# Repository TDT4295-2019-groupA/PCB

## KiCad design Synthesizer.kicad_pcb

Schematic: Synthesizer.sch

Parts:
C1: 150u; C_1206_3216Metric_Pad1.42x1.75mm_HandSolder
C2: 100n; C_0805_2012Metric_Pad1.15x1.40mm_HandSolder
D1, D2, D3, D4: LED; LED_D3.0mm
FB1, FB3, FB4: Ferrite_Bead; FerriteBead_74279215
J1: USB_A; TE_1932638-3
J2: AudioJack3; Jack_3.5mm_CUI_SJ-3524-SMT_Horizontal
J3: USB_B_Micro; USB_Micro-B_GCT_USB3076-30-A
R33, R34: 33; R_1206_3216Metric_Pad1.42x1.75mm_HandSolder
R38: 100; R_1206_3216Metric_Pad1.42x1.75mm_HandSolder
R39: 160; R_1206_3216Metric_Pad1.42x1.75mm_HandSolder
R40: 250; R_1206_3216Metric_Pad1.42x1.75mm_HandSolder
R41: 400; R_1206_3216Metric_Pad1.42x1.75mm_HandSolder
SW1, SW2, SW3, SW4, SW5, SW6, SW7, SW8, SW9, SW10, SW11, SW12, SW13, SW14, SW15, SW16: SW_Push; SW_Push_1P1T_NO_6x6mm_H9.5mm
U1: TPD3S014; SOT-23-6

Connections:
+3V3: SW1.1, SW2.1, SW3.1, SW4.1, SW5.1, SW6.1, SW7.1, SW8.1, SW9.1, SW10.1, SW11.1, SW12.1, SW13.1, SW14.1, SW15.1, SW16.1; also elsewhere on the board
+5V: C2.2, J3.1, U1.3; also elsewhere on the board
/Artix7/GREEN_LED: D4.2; also elsewhere on the board
/Artix7/RED_LED: D3.2; also elsewhere on the board
/Audio DAC/OUTL: J2.R; also elsewhere on the board
/Audio DAC/OUTR: J2.T; also elsewhere on the board
/Button0: SW13.2; also elsewhere on the board
/Button1: SW1.2; also elsewhere on the board
/Button2: SW2.2; also elsewhere on the board
/Button3: SW3.2; also elsewhere on the board
/Button4: SW4.2; also elsewhere on the board
/Button5: SW5.2; also elsewhere on the board
/Button6: SW6.2; also elsewhere on the board
/Button7: SW7.2; also elsewhere on the board
/Button8: SW8.2; also elsewhere on the board
/Button9: SW9.2; also elsewhere on the board
/Button10: SW10.2; also elsewhere on the board
/Button11: SW11.2; also elsewhere on the board
/Button12: SW12.2; also elsewhere on the board
/Button13: SW15.2; also elsewhere on the board
/Button14: SW14.2; also elsewhere on the board
/Button15: SW16.2; also elsewhere on the board
/EFM32/GREEN_LED: D2.2; also elsewhere on the board
/EFM32/RED_LED: D1.2; also elsewhere on the board
/EFM32/USB_D+: R33.1; also elsewhere on the board
/EFM32/USB_D-: R34.1; also elsewhere on the board
/EFM32/USB_VBUSEN: U1.1; also elsewhere on the board
GND: C1.1, C2.1, FB1.2, FB4.2, J2.S, J3.5, J3.6, R38.1, R39.1, R40.1, R41.1, U1.2; also elsewhere on the board
unnamed: C1.2, FB3.2, J1.1
unnamed: D1.1, R38.2
unnamed: D2.1, R39.2
unnamed: D3.1, R40.2
unnamed: D4.1, R41.2
unnamed: FB1.1, J1.4
unnamed: FB3.1, U1.4
unnamed: FB4.1, J1.5
unnamed: J1.2, R34.2, U1.5
unnamed: J1.3, R33.2, U1.6

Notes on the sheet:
PCM audio source
assuming source = 8mA
resistance assuming source = 20mA

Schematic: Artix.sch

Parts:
C3, C4: 100n; C_0805_2012Metric_Pad1.15x1.40mm_HandSolder
J4: FPGA_debug; PinHeader_2x07_P2.54mm_Vertical
J7: FPGA_GPIO; 67997-410HLF
R1: 2.4k; R_1206_3216Metric_Pad1.42x1.75mm_HandSolder
R2, R4: 10k; R_1206_3216Metric_Pad1.42x1.75mm_HandSolder
R3, R5, R6, R8: 4.7k; R_1206_3216Metric_Pad1.42x1.75mm_HandSolder
R7: 330; R_1206_3216Metric_Pad1.42x1.75mm_HandSolder
U2: S25FL127S; SOIC-8-1EP_3.9x4.9mm_P1.27mm_EP2.41x3.81mm
U3: XC7A100T-FTG256; Xilinx_FTG256
U4: Oscillator; Oscillator_SMD_Abracon_ASCO-4Pin_1.6x1.2mm

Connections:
+1V0: U3.E10, U3.F7, U3.F9, U3.F11, U3.G6, U3.H9, U3.J6, U3.K9, U3.L8; also elsewhere on the board
+1V8: U3.G8, U3.G10, U3.J10, U3.K11, U3.L10; also elsewhere on the board
+3V3: C3.1, C4.1, J4.2, J7.1, R1.1, R2.1, R3.1, R4.1, R5.1, R6.1, R7.1, R8.1, U2.8, U3.E7, U3.L6, U3.L16, U3.M9, U3.M13, U3.N10, U3.P7, U3.R14, U3.T11, U4.1, U4.4; also elsewhere on the board
/Artix7/DAC_LRCK: U3.L13; also elsewhere on the board
/Artix7/DAC_SCK: U3.L14; also elsewhere on the board
/Artix7/GREEN_LED: U3.R16; also elsewhere on the board
/Artix7/RED_LED: U3.R15; also elsewhere on the board
/Artix7/SPI_CLK: U3.P15; also elsewhere on the board
/Artix7/SPI_CS: U3.P16; also elsewhere on the board
/Artix7/SPI_MISO: U3.N16; also elsewhere on the board
/Artix7/SPI_MOSI: U3.M16; also elsewhere on the board
/Audio DAC/Audio-data: U3.K13; also elsewhere on the board
/Audio DAC/Bit-clock: U3.M14; also elsewhere on the board
/EFM32/FPGA_Ready: R7.2, U3.H10; also elsewhere on the board
/EFM32/FPGA_Reset: R6.2, U3.L9; also elsewhere on the board
/EFM32/FPGA_extra_1: U3.T14; also elsewhere on the board
/EFM32/FPGA_extra_2: U3.N13, U3.T15; also elsewhere on the board
/EFM32/FPGA_extra_4: U3.P13; also elsewhere on the board
GND: C3.2, C4.2, J4.1, J4.3, J4.5, J4.7, J4.9, J4.11, J4.13, J7.10, U2.4, U3.A1, U3.A6, U3.A11, U3.A16, U3.B3, U3.B8, U3.B13, U3.C5, U3.C10, U3.C15, U3.D2, U3.D7, U3.D12, U3.E4, U3.E9, U3.E14, U3.F1, U3.F6, U3.F8, U3.F10, U3.F16, U3.G3, U3.G7, U3.G9, U3.G13, U3.H6, U3.H7, U3.H8, U3.H15, U3.J2, U3.J7, U3.J8, U3.J9, U3.J11, U3.J12, U3.K4, U3.K6, U3.K14, U3.L1, U3.L11, U3.L15, U3.M3, U3.M8, U3.M10, U3.M11, U3.N5, U3.N15, U3.P2, U3.P12, U3.R4, U3.R9, U3.T1, U3.T6, U3.T16, U4.2; also elsewhere on the board
unnamed: J4.4, R2.2, U3.M7
unnamed: J4.6, R4.2, U3.L7
unnamed: J4.8, U3.N8
unnamed: J4.10, U3.N7
unnamed: J7.2, U3.P8
unnamed: J7.3, U3.N6
unnamed: J7.4, U3.M6
unnamed: J7.5, U3.P9
unnamed: J7.6, U3.T13
unnamed: J7.7, U3.R10
unnamed: J7.8, U3.R11
unnamed: J7.9, U3.N9
unnamed: R1.2, U2.1, U3.L12
unnamed: R3.2, U2.3, U3.K15
unnamed: R5.2, U3.K10
unnamed: R8.2, U2.7, U3.K16
unnamed: U2.2, U3.J14
unnamed: U2.5, U3.J13
unnamed: U2.6, U3.E8
unnamed: U3.N11, U4.3

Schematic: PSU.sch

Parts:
C50, C51, C65, C66, C67, C68: 22u; C_1206_3216Metric_Pad1.42x1.75mm_HandSolder
C52, C58, C59: 10u; C_1206_3216Metric_Pad1.42x1.75mm_HandSolder
C53, C54, C57, C60, C63: 100n; C_0805_2012Metric_Pad1.15x1.40mm_HandSolder
C55: 3.3n; C_0805_2012Metric_Pad1.15x1.40mm_HandSolder
C56: 1u; C_0805_2012Metric_Pad1.15x1.40mm_HandSolder
C61: 100u; CP_Radial_D5.0mm_P2.00mm
C62: 1u; CP_Radial_D4.0mm_P1.50mm
C64: 100n; C_1206_3216Metric_Pad1.42x1.75mm_HandSolder
FB5: Ferrite_Bead; FerriteBead_74279215
L1, L3: 1.5u; L_SPM3015
L2: 2.2u; L_SPM3015
R9: 30.1k; R_1206_3216Metric_Pad1.42x1.75mm_HandSolder
R10, R13, R16: 22.1k; R_1206_3216Metric_Pad1.42x1.75mm_HandSolder
R11, R14: 100k; R_1206_3216Metric_Pad1.42x1.75mm_HandSolder
R12: 6.81k; R_1206_3216Metric_Pad1.42x1.75mm_HandSolder
R15: 73.2k; R_1206_3216Metric_Pad1.42x1.75mm_HandSolder
R17: 1; R_1206_3216Metric_Pad1.42x1.75mm_HandSolder
U5: TPS54325; TSSOP-14-1EP_4.4x5mm_P0.65mm
U6: TPS54294; HTSSOP-16-1EP_4.4x5mm_P0.65mm_EP3x3mm

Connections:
+1V0: C65.1, C66.1, L3.2, R12.2, U5.1; also elsewhere on the board
+1V8: C50.1, C51.1, L1.1, R9.1; also elsewhere on the board
+3.3VA: R17.1; also elsewhere on the board
+3V3: C67.1, C68.1, FB5.1, L2.2, R15.1; also elsewhere on the board
+5V: C52.1, C53.1, C57.1, C58.1, C59.1, C60.1, C61.1, U5.7, U5.13, U5.14, U6.1, U6.16; also elsewhere on the board
GND: C50.2, C51.2, C52.2, C53.2, C55.2, C56.2, C57.2, C58.2, C59.2, C60.2, C61.2, C62.2, C65.2, C66.2, C67.2, C68.2, R10.2, R13.1, R16.2, U5.5, U5.8, U5.9, U5.15, U6.4, U6.8, U6.13, U6.17; also elsewhere on the board
unnamed: C54.1, U6.2
unnamed: C54.2, L1.2, U6.3
unnamed: C55.1, U5.4
unnamed: C56.1, R11.1, U5.3
unnamed: C62.1, R14.1, U6.9
unnamed: C63.1, L3.1, U5.10, U5.11
unnamed: C63.2, U5.12
unnamed: C64.1, U6.15
unnamed: C64.2, L2.1, U6.14
unnamed: FB5.2, R17.2
unnamed: R9.2, R10.1, U6.7
unnamed: R11.2, U5.6, U6.5
unnamed: R12.1, R13.2, U5.2
unnamed: R14.2, U6.6, U6.12
unnamed: R15.2, R16.1, U6.10

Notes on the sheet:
4.5V - 18V

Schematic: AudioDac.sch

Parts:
C69, C72, C73, C78: 100n; C_0805_2012Metric_Pad1.15x1.40mm_HandSolder
C70, C71: 2.2u; C_1206_3216Metric_Pad1.42x1.75mm_HandSolder
C74, C75, C76, C77: 10u; CP_Radial_D4.0mm_P1.50mm
C79, C80: 2.2n; C_0805_2012Metric_Pad1.15x1.40mm_HandSolder
R30, R31: 470; R_1206_3216Metric_Pad1.42x1.75mm_HandSolder
U8: PCM5102; TSSOP-20_4.4x6.5mm_P0.65mm

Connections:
+3.3VA: C75.1, C78.1, U8.8; also elsewhere on the board
+3V3: C69.1, C73.2, C74.1, C77.1, U8.1, U8.20; also elsewhere on the board
/Artix7/DAC_LRCK: U8.15; also elsewhere on the board
/Artix7/DAC_SCK: U8.12; also elsewhere on the board
/Audio DAC/Audio-data: U8.14; also elsewhere on the board
/Audio DAC/Bit-clock: U8.13; also elsewhere on the board
/Audio DAC/OUTL: C80.1, R30.1; also elsewhere on the board
/Audio DAC/OUTR: C79.1, R31.1; also elsewhere on the board
/Audio DAC/Soft-mute: U8.17; also elsewhere on the board
GND: C69.2, C70.2, C72.1, C73.1, C74.2, C75.2, C76.2, C77.2, C78.2, C79.2, C80.2, U8.3, U8.9, U8.10, U8.11, U8.16, U8.19; also elsewhere on the board
unnamed: C70.1, U8.5
unnamed: C71.1, U8.2
unnamed: C71.2, U8.4
unnamed: C72.2, C76.1, U8.18
unnamed: R30.2, U8.6
unnamed: R31.2, U8.7

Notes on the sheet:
PCM Audio Source
I don't know what these are
It's fine

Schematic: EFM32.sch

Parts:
C5: 100u; C_1206_3216Metric_Pad1.42x1.75mm_HandSolder
C6: 1u; C_0805_2012Metric_Pad1.15x1.40mm_HandSolder
FB2: Ferrite_Bead; FerriteBead_74279215
J5: MCU_debug; PinHeader_2x10_P2.54mm_Vertical
J6: MCU_GPIO; 67997-410HLF
RV1, RV2: R_POT; Potentiometer_Bourns_PRS11S_Vertical
U7: EFM32GG11B4xx; TQFP-64_10x10mm_P0.5mm
Y1: 48Mhz; Crystal_SMD_Abracon_L11.4mm_W4.70mm_2pin

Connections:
+3.3VA: U7.23, U7.27, U7.46; also elsewhere on the board
+3V3: J5.1, J6.1, RV1.1, RV2.3, U7.7, U7.26, U7.39, U7.55; also elsewhere on the board
+5V: FB2.1; also elsewhere on the board
/Artix7/SPI_CLK: U7.30; also elsewhere on the board
/Artix7/SPI_CS: U7.31; also elsewhere on the board
/Artix7/SPI_MISO: U7.29; also elsewhere on the board
/Artix7/SPI_MOSI: U7.28; also elsewhere on the board
/Audio DAC/Soft-mute: U7.2; also elsewhere on the board
/Button0: U7.3; also elsewhere on the board
/Button1: U7.4; also elsewhere on the board
/Button2: U7.5; also elsewhere on the board
/Button3: U7.6; also elsewhere on the board
/Button4: U7.9; also elsewhere on the board
/Button5: U7.10; also elsewhere on the board
/Button6: U7.11; also elsewhere on the board
/Button7: U7.12; also elsewhere on the board
/Button8: U7.13; also elsewhere on the board
/Button9: U7.14; also elsewhere on the board
/Button10: U7.15; also elsewhere on the board
/Button11: U7.16; also elsewhere on the board
/Button12: U7.17; also elsewhere on the board
/Button13: U7.18; also elsewhere on the board
/Button14: U7.19; also elsewhere on the board
/Button15: U7.21; also elsewhere on the board
/EFM32/FPGA_Ready: U7.38; also elsewhere on the board
/EFM32/FPGA_Reset: U7.37; also elsewhere on the board
/EFM32/FPGA_extra_1: U7.41; also elsewhere on the board
/EFM32/FPGA_extra_2: U7.42, U7.43; also elsewhere on the board
/EFM32/FPGA_extra_4: U7.44; also elsewhere on the board
/EFM32/GREEN_LED: U7.35; also elsewhere on the board
/EFM32/Overcurrent: U7.1
/EFM32/RED_LED: U7.34; also elsewhere on the board
/EFM32/USB_D+: U7.48; also elsewhere on the board
/EFM32/USB_D-: U7.47; also elsewhere on the board
/EFM32/USB_VBUSEN: U7.54; also elsewhere on the board
GND: C5.2, C6.1, J5.4, J5.6, J5.8, J5.10, J5.12, J5.14, J5.16, J5.18, J5.20, J6.10, U7.8, U7.22, U7.56; also elsewhere on the board
unnamed: C5.1, FB2.2, U7.52
unnamed: C6.2, U7.40
unnamed: J5.7, U7.50
unnamed: J5.9, U7.49
unnamed: J5.13, U7.51
unnamed: J5.15, U7.20
unnamed: J6.2, U7.58
unnamed: J6.3, U7.60
unnamed: J6.4, U7.62
unnamed: J6.5, U7.64
unnamed: J6.6, U7.57
unnamed: J6.7, U7.59
unnamed: J6.8, U7.61
unnamed: J6.9, U7.63
unnamed: RV1.2, U7.32
unnamed: RV2.2, U7.33
unnamed: U7.24, Y1.1
unnamed: U7.25, Y1.2

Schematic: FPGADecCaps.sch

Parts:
C12: 330u; CP_Radial_D6.3mm_P2.50mm
C13, C19: 100u; C_1206_3216Metric_Pad1.42x1.75mm_HandSolder
C14, C15: 47u; C_1206_3216Metric_Pad1.42x1.75mm_HandSolder
C16, C17, C20, C21, C24, C25, C27, C28, C31, C33, C39, C41: 4.7u; C_1206_3216Metric_Pad1.42x1.75mm_HandSolder
C18, C22, C23, C26, C29, C30, C32, C34, C35, C36, C37, C38, C40, C42, C43, C44, C45, C46, C47, C48, C49: 470n; C_0805_2012Metric_Pad1.15x1.40mm_HandSolder

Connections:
+1V0: C12.1, C13.1, C17.1, C18.1, C21.1, C22.1, C25.1, C28.1, C31.1, C33.1, C35.1, C37.1, C38.1, C40.1, C42.1, C44.1, C46.1, C48.1; also elsewhere on the board
+1V8: C14.1, C16.1, C20.1, C23.1, C26.1, C29.1; also elsewhere on the board
+3V3: C15.1, C19.1, C24.1, C27.1, C30.1, C32.1, C34.1, C36.1, C39.1, C41.1, C43.1, C45.1, C47.1, C49.1; also elsewhere on the board
GND: C12.2, C13.2, C14.2, C15.2, C16.2, C17.2, C18.2, C19.2, C20.2, C21.2, C22.2, C23.2, C24.2, C25.2, C26.2, C27.2, C28.2, C29.2, C30.2, C31.2, C32.2, C33.2, C34.2, C35.2, C36.2, C37.2, C38.2, C39.2, C40.2, C41.2, C42.2, C43.2, C44.2, C45.2, C46.2, C47.2, C48.2, C49.2; also elsewhere on the board

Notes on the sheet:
Vccint
Vccbram
Vccaux
Vcco

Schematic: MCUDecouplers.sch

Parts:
C7, C8, C10, C11, C81, C82: 100n; C_0805_2012Metric_Pad1.15x1.40mm_HandSolder
C9, C83: 10u; CP_Radial_D4.0mm_P1.50mm

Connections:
+3.3VA: C7.1, C8.1, C9.1; also elsewhere on the board
+3V3: C10.1, C11.1, C81.1, C82.1, C83.1; also elsewhere on the board
GND: C7.2, C8.2, C9.2, C10.2, C11.2, C81.2, C82.2, C83.2; also elsewhere on the board

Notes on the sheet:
decouplers for the MCU

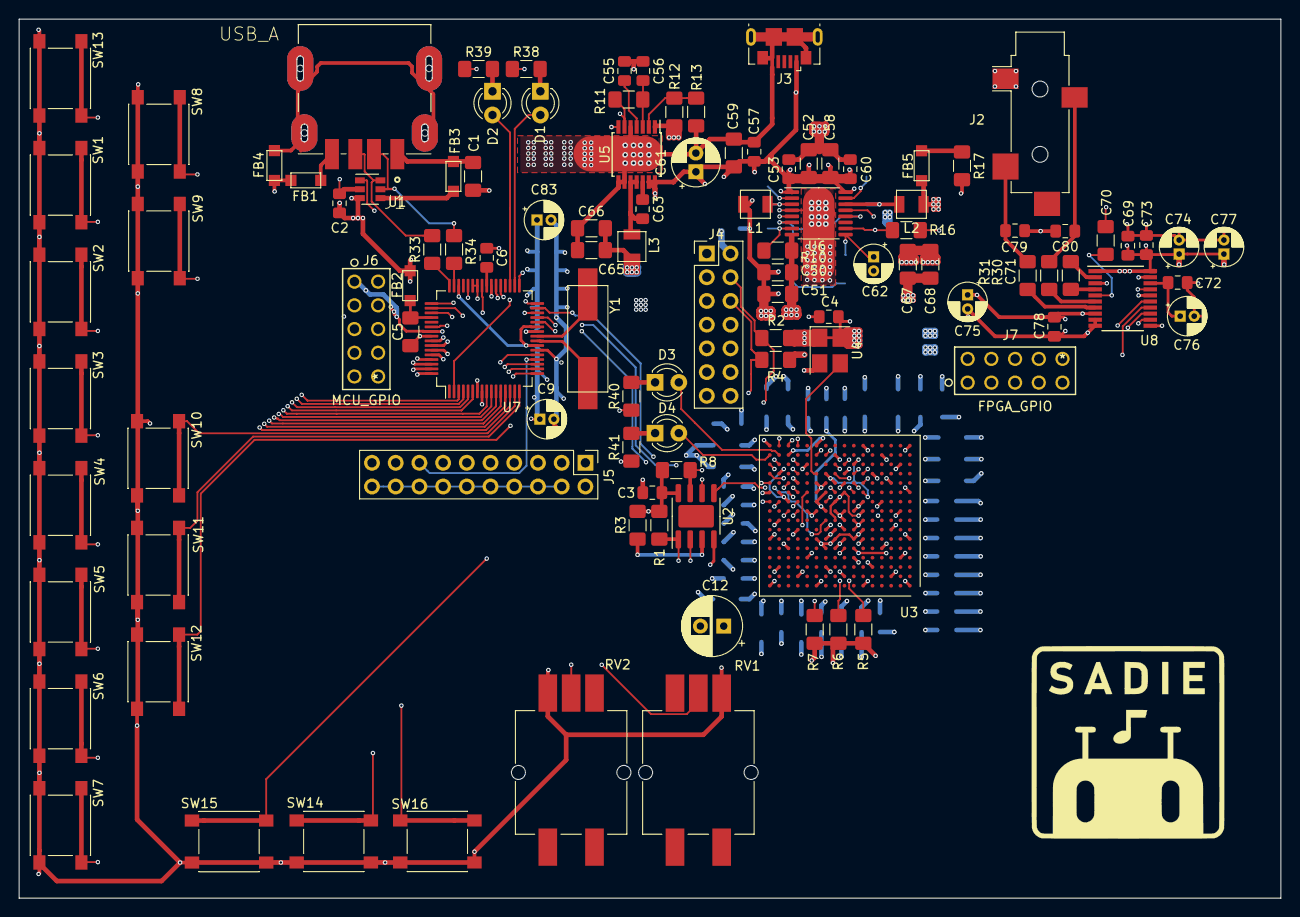
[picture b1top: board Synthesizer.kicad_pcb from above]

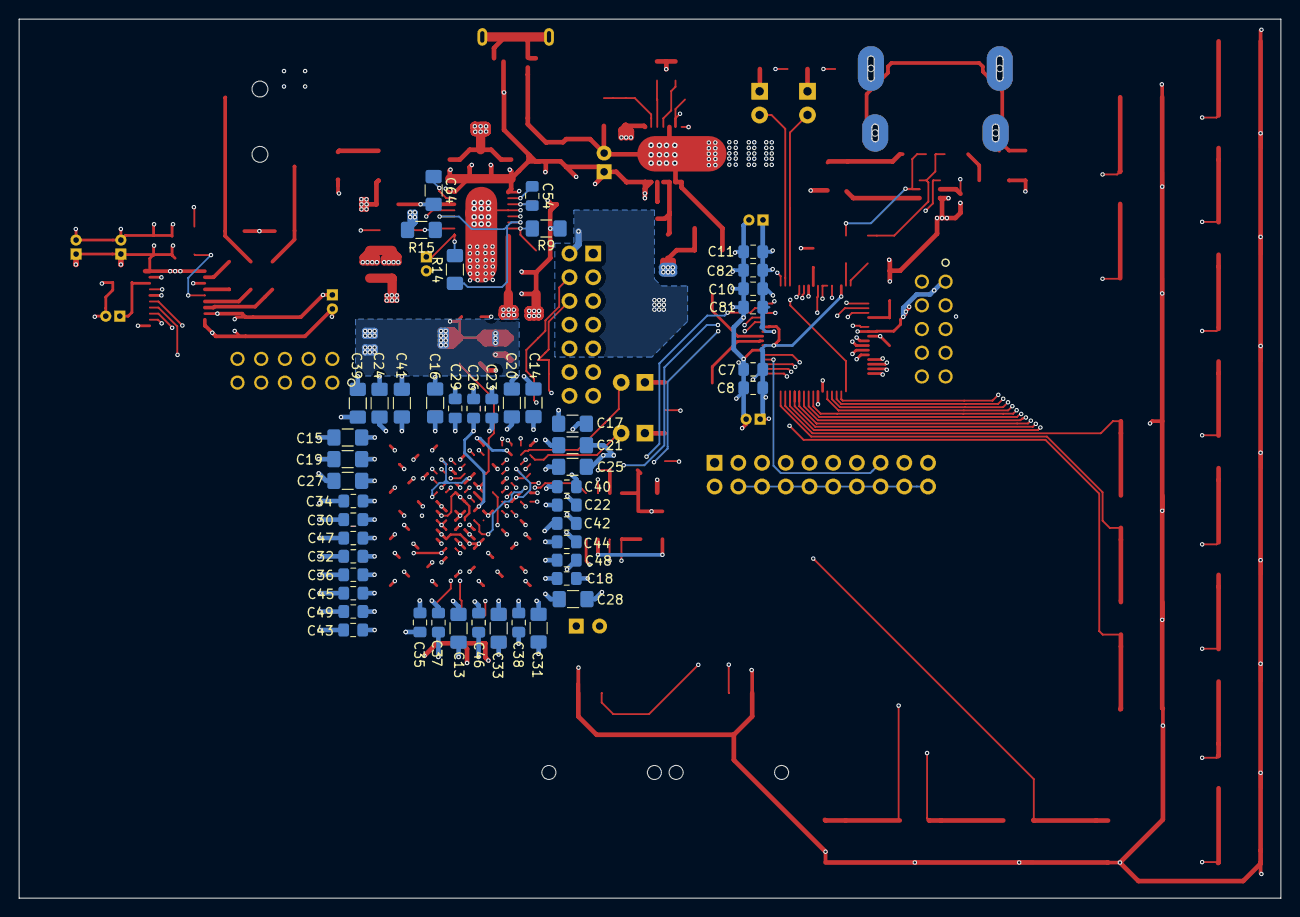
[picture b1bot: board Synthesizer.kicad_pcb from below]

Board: 6 copper layers, 135.2 x 94.2 mm, 154 parts (48 on the bottom side), 114 nets.

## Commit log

2019-09-12 init
2019-09-12 Added EFM32GG11 symbol
2019-09-12 Add .gitignore and remove unnecessary cache files
2019-09-12 Split EFM32GG symbol, creating one unit (D) exclusively for power connectors The rest are placeholders until we know how it makes sense to split them up. The lecture slides had 4 units, so i set it t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
2019-09-12 La til hele Artix7-kretsen
2019-09-12 Extra decouplers in FPGA-sheet
2019-09-12 add decouplers for MCU and connect them to unit D
2019-09-13 Add capacitors to FPGA Decouplers to match datasheet for XC7A100T Split up the Vcco capacitors again into the banks as described in the datasheet. Copy a row of banks if we end up needing more io pin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
2019-09-13 Added TPS54294 schematic to the library.
2019-09-13 Added TPS54325 schematic to the library.
2019-09-13 Added PSU... I think...
2019-09-15 Mye har skjedd
2019-09-16 use +3.3V symbol instead of wires with labels in Artix.sch
2019-09-17 add _autosave* to gitignore
2019-09-17 Label POWER -> Power Symbol
2019-09-17 use power symbols for 1V0 1V8
2019-09-17 Buttons+Pulldowns
2019-09-17 Starten på et PCB layout
2019-09-17 split EFM32GG into units for AB, C, D, EF
2019-09-17 Fixed FPGA decouplers so they deliver power. Removed Synthesizer-cache lib.
2019-09-17 Removed empty PowerSupply schematic.
2019-09-17 Added DAC subsheet.
2019-09-18 correct pins on MCU symbol unit C
2019-09-18 Updated DAC pin names, wired some to ground.
2019-09-18 Onsdags-commit
2019-09-18 Fikset symboler som forsvant
2019-09-18 Oopsy-woopsy fucky-wucky
2019-09-19 Better footprints
2019-09-19 Wired DAC to FPGA.
2019-09-19 La oss ta det litt piano, folkens
2019-09-19 Add library symbols for EFM32GG11B4xx
2019-09-19 Added audio jack and footprint
2019-09-19 Change the project to use the new MCU
2019-09-20 Connect the MCU SPI pins to FPGA
2019-09-20 Connect FPGA done and program_b pin to some pins on the MCU
2019-09-20 Add USB symbol and pins
2019-09-23 Wired up minijack and micro-USB.
2019-09-23 Wired USB-A. Added a capacitor to USB_VBUS in the schematic. No idea what to do about VBUSEN though.
2019-09-23 Added ESD protection to USB-A. Connected Soft-mute.
2019-09-23 Added power source for USB-A.
2019-09-23 Added forgotten USB-B power source, powered bank 14 of FPGA.
2019-09-23 Re-add SPI connections inside Artix sheet Thank mr. kicad for fantastic VCS support
2019-09-24 add placeholder footprints, clean up ratsnest a bit
2019-09-24 Connect buttons and move MCU->FPGA done/program_b pins
2019-09-25 Added NPN transistor on USB and wired shield. Added LEDs, debug pins.
2019-09-25 Fixed buttons, FPGA wires that were accidentally connected to GND.
2019-09-25 Add header for MCU GPIO
2019-09-25 Give footprints to LEDs
2019-09-25 Slight prettification
2019-09-25 Update PCB design rules
2019-09-26 Fix USB connections and various cleanup
2019-09-26 Rearrange PCB components to more closely match schematics and take up less space
2019-09-26 Added resistors on LEDs.
2019-09-26 Fixed LED bugs again. I think it's right now.
2019-09-26 Last fix to LEDs... Oops
2019-09-26 Fixed u being written as µ (my bad.) Tried doing work on the PSU but it's eldritch.
2019-09-26 Added crystal footprint. Also, moved REF on LED so it would be legible.
2019-09-26 Added bill of materials. Also, fixed one of the USB capacitors...
2019-09-26 Route tracks for buttons among other things
2019-09-27 Fixed crystal footprint to comply with recommended land pattern. Fixed merge.
2019-09-27 Added Ferride Bead footprint
2019-09-27 Updated component footprints. The PCB is now an unholy mess.
2019-09-27 Tag you're it. Wired up the DAC, fixed the PSU footprint.
2019-09-27 Added potentiometers to EFM32. Haven't updated the physical layout for it.
2019-09-27 I forgot to annotate things again
2019-09-27 Added in the potentiometers, fixed some faulty pins on the artix, rewired some pins on the MCU so they didn't interfere with the crystal.
2019-09-27 Wired up the potentiometers.
2019-09-27 Started wiring the flash chip.
2019-09-27 Fix via diameters to fit FPGA and fix some via connections
2019-09-27 Add vias to most FPGA pins and reroute many long surface traces through them
2019-09-27 Added 3.3V and GND power planes and started placing vias for them
2019-09-28 Revert "Added 3.3V and GND power planes and started placing vias for them"
    A lot of this has to be redone, and it'll be faster to revert everything than to undo most of it. Sorry.
    This reverts commit 094bcba739ea07dc7ad5aae56f3abc91d941740f.
2019-09-28 Added footprint for the coils we're using.
2019-09-28 Fixed coil footprint oops
2019-09-28 Wire up 1V PSU. Use smaller footprints for small caps.
2019-09-28 Added USB-A receptacle footprint.
2019-09-28 Wire up other PSU
2019-09-28 Rearrange and rewire most of the PCB
2019-09-29 Added in a bunch of footprints to the netlist; only missing buttons and some resistors, now.
2019-09-29 add missing button traces, tidy up labels a bit
2019-09-29 add logo draft(?)
2019-09-29 Revert "add logo draft(?)"
    This reverts commit 0874d0c373619f7d5d47854bd0a0fb4f43bdef77.
2019-09-29 Revert "add missing button traces, tidy up labels a bit"
    This reverts commit 2afccf877748aad07f819f0c8185ed7717c89559.
2019-09-29 Revert "Added in a bunch of footprints to the netlist; only missing buttons and some resistors, now."
    This reverts commit 26f31b12234d03a706d1f0abb84aa744ef749ada.
2019-09-29 Rearrange and wire most of PCB FOR REAL THIS TIME
2019-09-29 "Merge" footprint changes and netlist
2019-09-29 Readd logo
2019-09-29 Connect 3V pin of MCU GPIO
2019-09-29 Move one capacitor so it doesn't clip with a resistor
2019-09-29 Fix a few more noclipping objects and labels
2019-09-29 Fix floating "USB A" label
2019-09-29 Fix more noclipping components
2019-09-29 Forgot to save for the previous one
2019-09-30 Removed pull-down resistors.
2019-09-30 wire up buttons
2019-09-30 update logo
2019-09-30 Fixed pin header footprints, rewired. I think it's done?
2019-09-30 Fixed DRC errors. It's done
2019-09-30 Pushed up Micro-USB so it's on PCB edge.
2019-09-30 add back logo
2019-09-30 add labels for debug headers, fix some other labels
2019-09-30 Fix one erroneous trace. VERY REVOLUTIONARY CHANGES
2019-10-02 Changed a capacitor value from 100u to 150u. (oopsiedaisy)
2019-10-02 Replaced oscillator with a larger footprint and rewired. Also changed track width on some USB-A wires.
2019-10-02 Move FPGA decoupling caps. Rewire some PWR/GND pins
2019-10-03 add power planes, spam vias everywhere
2019-10-03 Thicken some power traces under the FPGA
2019-10-03 Thicken traces and thin planes
2019-10-03 Thicken 1.8V layer

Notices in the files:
parts and their libraries:
Copyright 2016 Accelerated Designs. All rights reserved.
